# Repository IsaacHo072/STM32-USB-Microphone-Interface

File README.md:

# STM32-USB-Microphone-Interface
USB Audio Class Device with STM32G431CB and TLV320ADC6120

The PCB is working, but not fully verified since the I2C + I2S driver for TLV320ADC6120 haven't been written yet.

Some changes needed to be made to the STM32 board, for revision B:
 - Move all components to the top of the board, so it could be reflowed at once
 - Change the USB-C connector to a more popular and cheaper one
 - RST button have the wrong footprint, missing the positioning hole
 
Software development:
| Task                                                        | Status      | Finished?                                                                       |
|-------------------------------------------------------------|-------------|---------------------------------------------------------------------------------|
| Setup STM32G431 as a USB Audio Class Device in STM32CubeIDE | in progress | <ul><li>[x] USB could connect to PC </li><li>[ ] USB microphone mode </li></ul> |
| TLV320ADC6120 I2C Control                                   |             |                                                                                 |
| TLV320ADC6120 I2S transfer with DMA                         |             |                                                                                 |

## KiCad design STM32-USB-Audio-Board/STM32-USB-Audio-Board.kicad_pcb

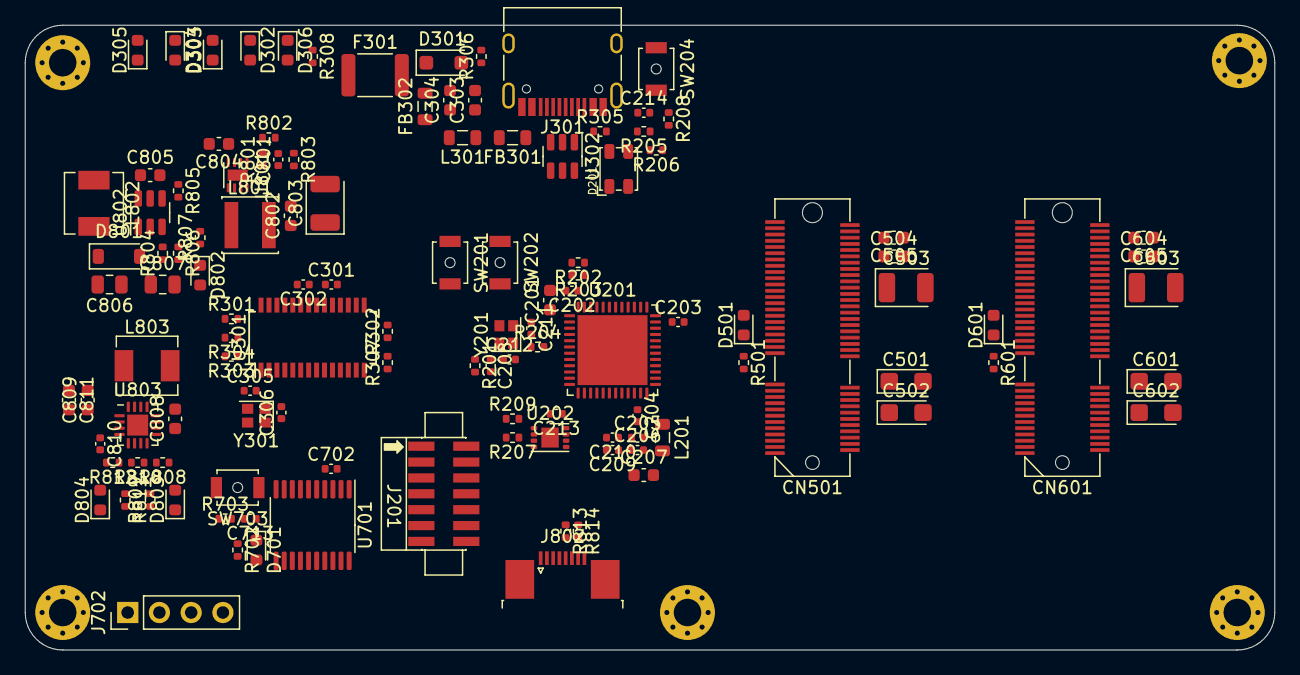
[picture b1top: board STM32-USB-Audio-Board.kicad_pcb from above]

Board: 4 copper layers, 100.0 x 50.0 mm, 125 parts (0 on the bottom side), 99 nets, no tracks yet.

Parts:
C201, C207, C303, C304, C802, C808, C811: 4.7uF; C_0603_1608Metric
C202, C203, C204, C206, C208, C210, C213, C214, C301, C302, C702, C810: 100nF; C_0402_1005Metric
C205: 1nF; C_0402_1005Metric
C209: 1uF; C_0402_1005Metric
C211, C212, C305, C306: 12pF; C_0402_1005Metric
C501, C502, C601, C602: 10uF; CP_EIA-3216-18_Kemet-A
C503, C603, C803: 10uF; CP_EIA-3528-21_Kemet-B
C504, C505, C604, C605, C804, C805, C809: 10uF; C_0603_1608Metric
C713: 10nF; C_0402_1005Metric
C801: 10pF; C_0402_1005Metric
C806, C807: 10uF; C_0805_2012Metric
CN501, CN601: Conn_02x38_Odd_Even; APCI0143-P001A
D201: LED_Dual_KAKA; LED_Dual_3528
D301: 20V; D_SOD-123F
D302, D303, D304, D305: GREEN; LED_0603_1608Metric
D306: RED; LED_0603_1608Metric
D501, D601, D701, D802, D803, D804: LED; LED_0603_1608Metric
D801: 3A/40V; D_SOD-123
F301: 2A; Fuse_1812_4532Metric
FB301, FB302: 100R; L_0805_2012Metric
H101, H102, H103, H104, H105: MountingHole_Pad; MountingHole_2.2mm_M2_Pad_Via
J201: Conn_ST_STDC14; STDC14_2x07_P1.27mm_Vertical_SMD
J301: USB_C_Receptacle_USB2.0; USB_C_Receptacle_HRO_TYPE-C-31-M-12
J702: Conn_01x04; PinHeader_1x04_P2.54mm_Vertical
J802: Conn_01x08; TE_0-1734839-8_1x08-1MP_P0.5mm_Horizontal
L201: 5R; L_0805_2012Metric
L301: 1.2uH; L_0805_2012Metric
L801: 1uH; L_Sunlord_SWPA4020S
L802: 10uH; L_Sunlord_MWSA0412S
L803: 2.2uH; L_Sunlord_MWSA0412S
R201: 0R; R_0402_1005Metric
R202, R203: 3.3k; R_0402_1005Metric
R204, R303, R304, R308, R702: 1k; R_0402_1005Metric
R205, R206: 2k; R_0402_1005Metric
R207, R209, R801, R802, R805: 100k; R_0402_1005Metric
R208, R301, R302, R703, R807: 10k; R_0402_1005Metric
R305, R306: 5.1k; R_0402_1005Metric
R307, R501, R601, R809, R811: 2.7k; R_0402_1005Metric
R803: 22.1k; R_0402_1005Metric
R804: 220k; R_0402_1005Metric
R806: 9.1k; R_0402_1005Metric
R808: 365k; R_0402_1005Metric
R810: 120k; R_0402_1005Metric
R812: 487k; R_0402_1005Metric
R813, R814: 100R; R_0402_1005Metric
SW201, SW202, SW204, SW703: SW_Push; SW_SPST_B3U-1000P-B
U201: STM32G431CBUx; QFN-48-1EP_7x7mm_P0.5mm_EP5.6x5.6mm
U202: W25Q16; SON-8-1EP_3x2mm_P0.5mm_EP1.4x1.6mm
U301: FE1.1s; SSOP-28_3.9x9.9mm_P0.635mm
U302: USBLC6-2SC6; SOT-23-6
U701: CH32V203F8P6; TSSOP-20_4.4x6.5mm_P0.65mm
U801: SY8883DFC; DFN-8-1EP_2x2mm_P0.5mm_EP0.9x1.6mm
U802: SY7208; SOT-23-6
U803: TPS65135; WQFN-16-1EP_3x3mm_P0.5mm_EP1.68x1.68mm
Y201: 8MHz; Crystal_SMD_2016-4Pin_2.0x1.6mm
Y301: 12MHz; Crystal_SMD_2016-4Pin_2.0x1.6mm

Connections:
+3.3V: C201.1, C202.1, C203.1, C204.1, C213.1, C501.1, C502.1, C601.1, C602.1, C702.1, C801.1, C802.1, C803.1, C809.1, CN501.18, CN501.20, CN501.22, CN601.18, CN601.20, CN601.22, D501.2 (A), D601.2 (A), J201.3 (VCC), J702.1, L201.1, L801.2, R202.2, R203.2, R205.1, R206.1, R208.2, R209.1, R703.1, R801.1, U201.1 (VBAT), U201.23 (VDD), U201.35 (VDD), U201.48 (VDD), U202.3 (IO2), U202.7 (IO3), U202.8 (VCC), U701.4 (VDD), U803.1 (VIN), U803.8 (EN)
+5V: C301.1, C804.1, C805.1, CN501.10, CN501.12, CN601.10, CN601.12, F301.1, J802.2, J802.3, L802.1, R802.1, R805.1, U301.18 (VBUSM), U301.20 (VDD5), U801.3 (IN), U802.5 (IN)
+5VA: C504.1, C604.1, C808.1, CN501.64, CN601.64, D803.2 (A), R808.1, U803.9 (OUTP), U803.10 (OUTP)
+15V: C503.1, C603.1, C806.1, C807.1, CN501.58, CN501.60, CN601.58, CN601.60, D801.1 (K), D802.2 (A), R804.1
-5VA: C505.2, C605.2, C811.2, CN501.70, CN601.70, D804.2 (A), R812.2, U803.2 (OUTN), U803.3 (OUTN)
/DAPLink CH32V203/LED_SWD: D701.2 (A), U701.12 (PA5)
/DAPLink CH32V203/RX1: J702.3, U701.20 (PA10)
/DAPLink CH32V203/SWD_RST: R201.1, U701.11 (PA4)
/DAPLink CH32V203/TX1: J702.2, U701.19 (PA9)
/DAPLink CH32V203/USB_DN: U301.10 (DM1), U701.1 (PB6)
/DAPLink CH32V203/USB_DP: U301.11 (DP1), U701.2 (PB7)
/HMI Sub-board Connector/Host_RX: R814.1, U201.24 (PB11)
/HMI Sub-board Connector/Host_TX: R813.1, U201.22 (PB10)
/Power Supply/3VEN: R802.2, U801.7 (EN)
/Power Supply/FB: C801.2, R801.2, R803.1, U801.1 (FB)
/Power Supply/LX: L801.1, U801.6 (LX)
/STM32G431CBU6/CARD_DETECT_0: CN501.23, U201.25 (PB12)
/STM32G431CBU6/CARD_DETECT_1: CN601.23, U201.26 (PB13)
/STM32G431CBU6/I2C1_SCL: CN501.54, CN601.54, R202.1, SW202.2, U201.46 (PB8)
/STM32G431CBU6/I2C1_SDA: CN501.52, CN601.52, R203.1, U201.47 (PB9)
/STM32G431CBU6/NRST: C208.2, J201.12 (~RST), R201.2, SW201.2, U201.7 (PG10)
/STM32G431CBU6/RCC_OSC_IN: C211.2, U201.5 (PF0), Y201.3
/STM32G431CBU6/RCC_OSC_OUT: R204.2, U201.6 (PF1)
/STM32G431CBU6/SAI-A-FS: CN501.36, U201.31 (PA9)
/STM32G431CBU6/SAI-A-GPIO0: CN501.46, U201.29 (PC6)
/STM32G431CBU6/SAI-A-GPIO1: CN501.48, U201.28 (PB15)
/STM32G431CBU6/SAI-A-MCLK: CN501.42, U201.11 (PA3)
/STM32G431CBU6/SAI-A-SCK: CN501.34, U201.30 (PA8)
/STM32G431CBU6/SAI-A-SD: CN501.38, U201.32 (PA10)
/STM32G431CBU6/SAI-B-FS: CN601.36, U201.44 (PB6)
/STM32G431CBU6/SAI-B-GPIO0: CN601.46, U201.39 (PC10)
/STM32G431CBU6/SAI-B-GPIO1: CN601.48, U201.40 (PC11)
/STM32G431CBU6/SAI-B-MCLK: CN601.42, U201.42 (PB4)
/STM32G431CBU6/SAI-B-SCK: CN601.34, U201.41 (PB3)
/STM32G431CBU6/SAI-B-SD: CN601.38, U201.43 (PB5)
/STM32G431CBU6/SPI_MISO: R207.1, U201.14 (PA6), U202.2 (DO(IO1))
/STM32G431CBU6/SPI_MOSI: U201.15 (PA7), U202.5 (DI(IO0))
/STM32G431CBU6/SPI_NSS: R209.2, U201.12 (PA4), U202.1 (~CS)
/STM32G431CBU6/SPI_SCK: U201.13 (PA5), U202.6 (CLK)
/STM32G431CBU6/SWCLK: J201.6 (JCLK/SWCLK), U201.37 (PA14), U701.7 (PA1)
/STM32G431CBU6/SWDIO: J201.4 (JTMS/SWDIO), U201.36 (PA13), U701.6 (PA0)
/STM32G431CBU6/USART1_RX: J201.13 (VCP_RX), U201.45 (PB7), U701.8 (PA2)
/STM32G431CBU6/USART1_TX: J201.14 (VCP_TX), U201.16 (PC4), U701.9 (PA3)
/STM32G431CBU6/USB_DN: U201.33 (PA11), U301.6 (DM3)
/STM32G431CBU6/USB_DP: U201.34 (PA12), U301.7 (DP3)
/STM32G431CBU6/USER_LED_G: D201.1 (A1), U201.18 (PB1)
/STM32G431CBU6/USER_LED_R: D201.3 (A2), U201.17 (PB0)
/STM32G431CBU6/VDDA: C205.1, C206.1, C207.1, L201.2, U201.21 (VDDA)
/STM32G431CBU6/VREF: C209.1, C210.1, U201.20 (VREF+)
/Sub-Board Connector 1/CARD_DETECT1: CN501.21, R501.2
/Sub-Board Connector 1/USB_DN: CN501.5, U301.8 (DM2)
/Sub-Board Connector 1/USB_DP: CN501.3, U301.9 (DP2)
/Sub-Board Connector 2/CARD_DETECT1: CN601.21, R601.2
/Sub-Board Connector 2/USB_DN: CN601.5, U301.4 (DM4)
/Sub-Board Connector 2/USB_DP: CN601.3, U301.5 (DP4)
/USB Connector/FE1.1_3.3V: C302.1, R301.1, R302.1, U301.21 (VD33_O)
/USB Connector/USB_DN: U301.15 (DMU), U302.6 (I/O1)
/USB Connector/USB_DP: U301.16 (DPU), U302.4 (I/O2)
/USB Connector/USBc_DN: J301.A7 (D-), J301.B7 (D-), U302.1 (I/O1)
/USB Connector/USBc_DP: J301.A6 (D+), J301.B6 (D+), U302.3 (I/O2)
/USB Connector/VBUS: D301.1 (A1), F301.2, FB302.2
/USB Connector/VBUS_{C}: FB301.1, J301.A4 (VBUS), J301.A9 (VBUS), J301.B4 (VBUS), J301.B9 (VBUS)
GND: C201.2, C202.2, C203.2, C204.2, C205.2, C206.2, C207.2, C208.1, C209.2, C210.2, C211.1, C212.1, C213.2, C214.1, C301.2, C302.2, C303.2, C304.2, C305.1, C306.1, C501.2, C502.2, C503.2, C504.2, C505.1, C601.2, C602.2, C603.2, C604.2, C605.1, C702.2, C713.1, C802.2, C803.2, C804.2, C805.2, C806.2, C807.2, C808.2, C809.2, C810.2, C811.1, CN501.1, CN501.2, CN501.4, CN501.6, CN501.7, CN501.8, CN501.9, CN501.11, CN501.13, CN501.14, CN501.15, CN501.16, CN501.17, CN501.19, CN501.32, CN501.33, CN501.35, CN501.37, CN501.39, CN501.41, CN501.43, CN501.44, CN501.45, CN501.47, CN501.49, CN501.50, CN501.51, CN501.53, CN501.55, CN501.56, CN501.57, CN501.59, CN501.61, CN501.62, CN501.63, CN501.65, CN501.66, CN501.67, CN501.68, CN501.69, CN501.71, CN501.72, CN501.73, CN501.74, CN501.75, CN601.1, CN601.2, CN601.4, CN601.6, CN601.7, CN601.8, CN601.9, CN601.11, CN601.13, CN601.14, CN601.15, CN601.16, CN601.17, CN601.19, CN601.32, CN601.33, CN601.35, CN601.37, CN601.39, CN601.41, CN601.43, CN601.44, CN601.45, CN601.47, CN601.49, CN601.50, CN601.51, CN601.53, CN601.55, CN601.56, CN601.57, CN601.59, CN601.61, CN601.62, CN601.63, CN601.65, CN601.66, CN601.67, CN601.68, CN601.69, CN601.71, CN601.72, CN601.73, CN601.74, CN601.75, D301.2 (A2), H101.1, H102.1, H103.1, H104.1, H105.1, J201.5 (GND), J201.7 (GND), J301.A1 (GND), J301.A12 (GND), J301.B1 (GND), J301.B12 (GND), J702.4, J802.1, J802.4, J802.6, J802.8, R207.2, R305.2, R306.2, R307.2, R308.2, R702.2, R803.2, R806.2, R807.2, R809.2, R811.2, SW201.1, SW202.1, SW204.1, SW703.2, U201.49 (VSS), U202.4 (GND), U301.1 (VSS), U301.19 (BUSJ), U302.2 (GND), U701.3 (VSS), U801.4 (PGND), U801.8 (AGND), U801.9 (PGND), U802.2 (GND), U803.5 (GND), U803.11 (PGND), U803.12 (PGND), U803.17 (EP), Y201.2, Y201.4, Y301.2, Y301.4
unnamed: C212.2, R204.1, Y201.1
unnamed: C303.1, FB301.2, L301.1
unnamed: C304.1, FB302.1, L301.2
unnamed: D201.2 (K1), R205.2
unnamed: D201.4 (K2), R206.2
unnamed: D302.2 (A), D303.1 (K), D304.2 (A), D305.1 (K), D306.2 (A), U301.22 (DRV)
unnamed: D302.1 (K), D303.2 (A), R303.2
unnamed: D304.1 (K), D305.2 (A), R304.2
unnamed: D306.1 (K), R308.1
unnamed: D501.1 (K), R501.1
unnamed: D601.1 (K), R601.1
unnamed: D701.1 (K), R702.1
unnamed: D801.2 (A), L802.2, U802.1 (LX)
unnamed: D802.1 (K), R807.1
unnamed: D803.1 (K), R809.1
unnamed: D804.1 (K), R811.1
unnamed: J301.A5 (CC1), R305.1
unnamed: J301.B5 (CC2), R306.1
unnamed: J802.5, R813.2
unnamed: J802.7, R814.2
unnamed: L803.1, U803.15 (L1), U803.16 (L1)
unnamed: L803.2, U803.13 (L2), U803.14 (L2)
unnamed: C214.2, R208.1, SW204.2, U201.27 (PB14)
unnamed: R303.1, U301.23 (LED1/EESCL)
unnamed: R304.1, U301.24 (LED2)
unnamed: R301.2, U301.26 (OVCJ)
unnamed: R307.1, U301.14 (REXT)
unnamed: C306.2, U301.3 (XIN), Y301.1
unnamed: C305.2, U301.2 (XOUT), Y301.3
unnamed: R302.2, U301.17 (~XRSTJ)
unnamed: C713.2, R703.2, SW703.1, U701.5 (NRST)
unnamed: R805.2, U802.4 (EN)
unnamed: R804.2, R806.1, U802.3 (FB)
unnamed: R808.2, R810.1, U803.7 (FB)
unnamed: R810.2, R812.1, U803.6 (FBG)
unnamed: C810.1, U803.4 (VAUX)

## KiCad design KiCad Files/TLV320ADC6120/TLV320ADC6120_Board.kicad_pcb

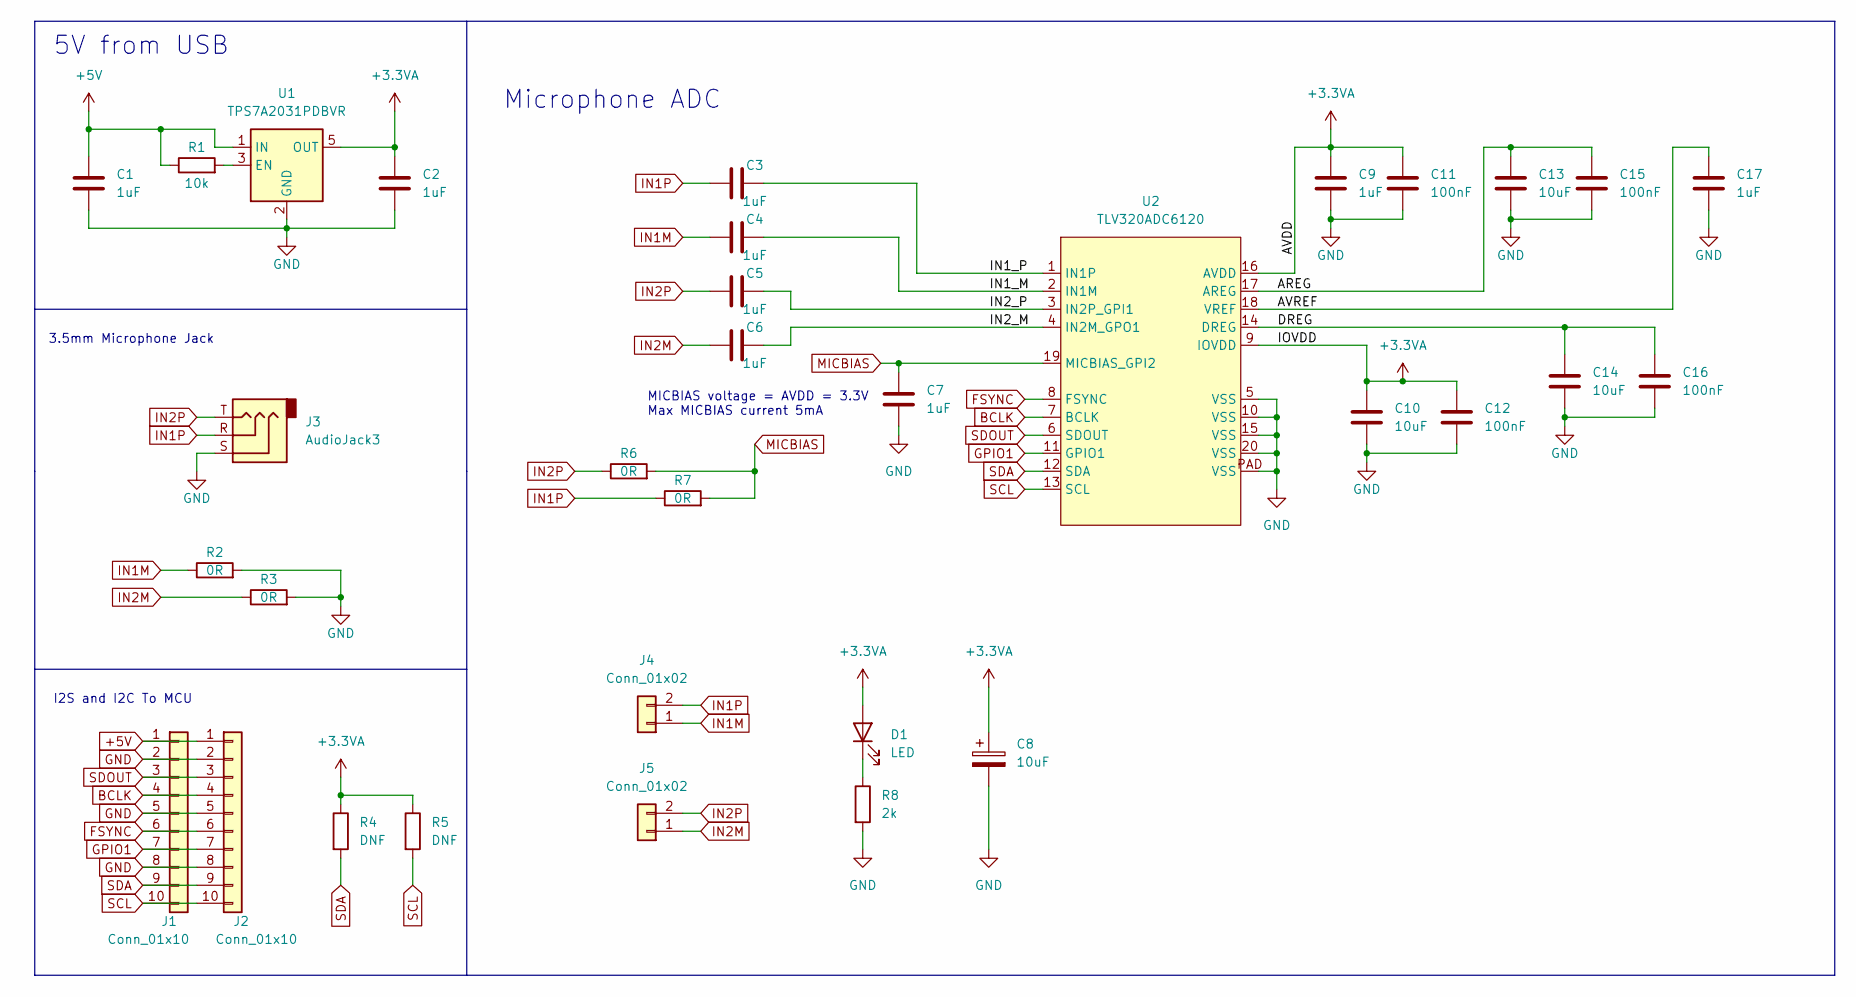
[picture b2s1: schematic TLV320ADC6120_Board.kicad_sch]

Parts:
C1, C2, C7, C9, C17: 1uF; C_0603_1608Metric
C3, C4, C5, C6: 1uF; C_1206_3216Metric
C8: 10uF; CP_EIA-3216-18_Kemet-A
C10, C13, C14: 10uF; C_0603_1608Metric
C11, C12, C15, C16: 100nF; C_0402_1005Metric
D1: LED; LED_0603_1608Metric
J1: Conn_01x10; JST_PH_S10B-PH-SM4-TB_1x10-1MP_P2.00mm_Horizontal
J2: Conn_01x10; PinHeader_1x10_P2.00mm_Vertical
J3: AudioJack3; Jack_3.5mm_CUI_SJ-3523-SMT_Horizontal
J4, J5: Conn_01x02; JST_PH_B2B-PH-SM4-TB_1x02-1MP_P2.00mm_Vertical
R1: 10k; R_0603_1608Metric
R2, R3, R6, R7: 0R; R_0603_1608Metric
R4, R5: DNF; R_0603_1608Metric
R8: 2k; R_0603_1608Metric
U1: TPS7A2031PDBVR; SOT-23-5
U2: TLV320ADC6120; QFN-16_EP_3x3_Pitch0.5mm

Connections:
+3.3VA: C2.1, C8.1, C9.1, C10.1, C11.1, C12.1, D1.2 (A), R4.1, R5.1, U1.5 (OUT), U2.9 (IOVDD), U2.16 (AVDD)
+5V: C1.1, J1.1, J2.1, R1.1, U1.1 (IN)
/AREG: C13.1, C15.1, U2.17 (AREG)
/AVREF: C17.1, U2.18 (VREF)
/DREG: C14.1, C16.1, U2.14 (DREG)
/IN1_M: C4.2, U2.2 (IN1M)
/IN1_P: C3.2, U2.1 (IN1P)
/IN2_M: C6.2, U2.4 (IN2M_GPO1)
/IN2_P: C5.2, U2.3 (IN2P_GPI1)
BCLK: J1.4, J2.4, U2.7 (BCLK)
FSYNC: J1.6, J2.6, U2.8 (FSYNC)
GND: C1.2, C2.2, C7.2, C8.2, C9.2, C10.2, C11.2, C12.2, C13.2, C14.2, C15.2, C16.2, C17.2, J1.2, J1.5, J1.8, J2.2, J2.5, J2.8, J3.S, R2.2, R3.2, R8.2, U1.2 (GND), U2.5 (VSS), U2.10 (VSS), U2.15 (VSS), U2.20 (VSS), U2.PAD (VSS)
GPIO1: J1.7, J2.7, U2.11 (GPIO1)
IN1M: C4.1, J4.1, R2.1
IN1P: C3.1, J3.R, J4.2, R7.1
IN2M: C6.1, J5.1, R3.1
IN2P: C5.1, J3.T, J5.2, R6.1
MICBIAS: C7.1, R6.2, R7.2, U2.19 (MICBIAS_GPI2)
unnamed: D1.1 (K), R8.1
unnamed: R1.2, U1.3 (EN)
SCL: J1.10, J2.10, R5.2, U2.13 (SCL)
SDA: J1.9, J2.9, R4.2, U2.12 (SDA)
SDOUT: J1.3, J2.3, U2.6 (SDOUT)

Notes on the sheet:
3.5mm Microphone Jack
MICBIAS voltage = AVDD = 3.3V Max MICBIAS current 5mA
I2S and I2C To MCU
5V from USB
Microphone ADC

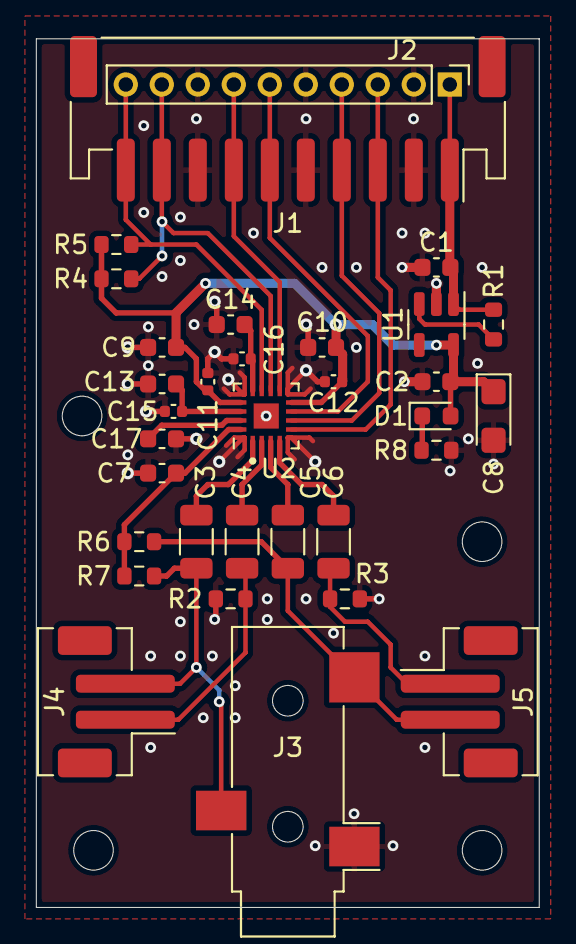
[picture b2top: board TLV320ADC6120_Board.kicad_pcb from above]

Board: 2 copper layers, 27.9 x 48.3 mm, 33 parts (0 on the bottom side), 23 nets.

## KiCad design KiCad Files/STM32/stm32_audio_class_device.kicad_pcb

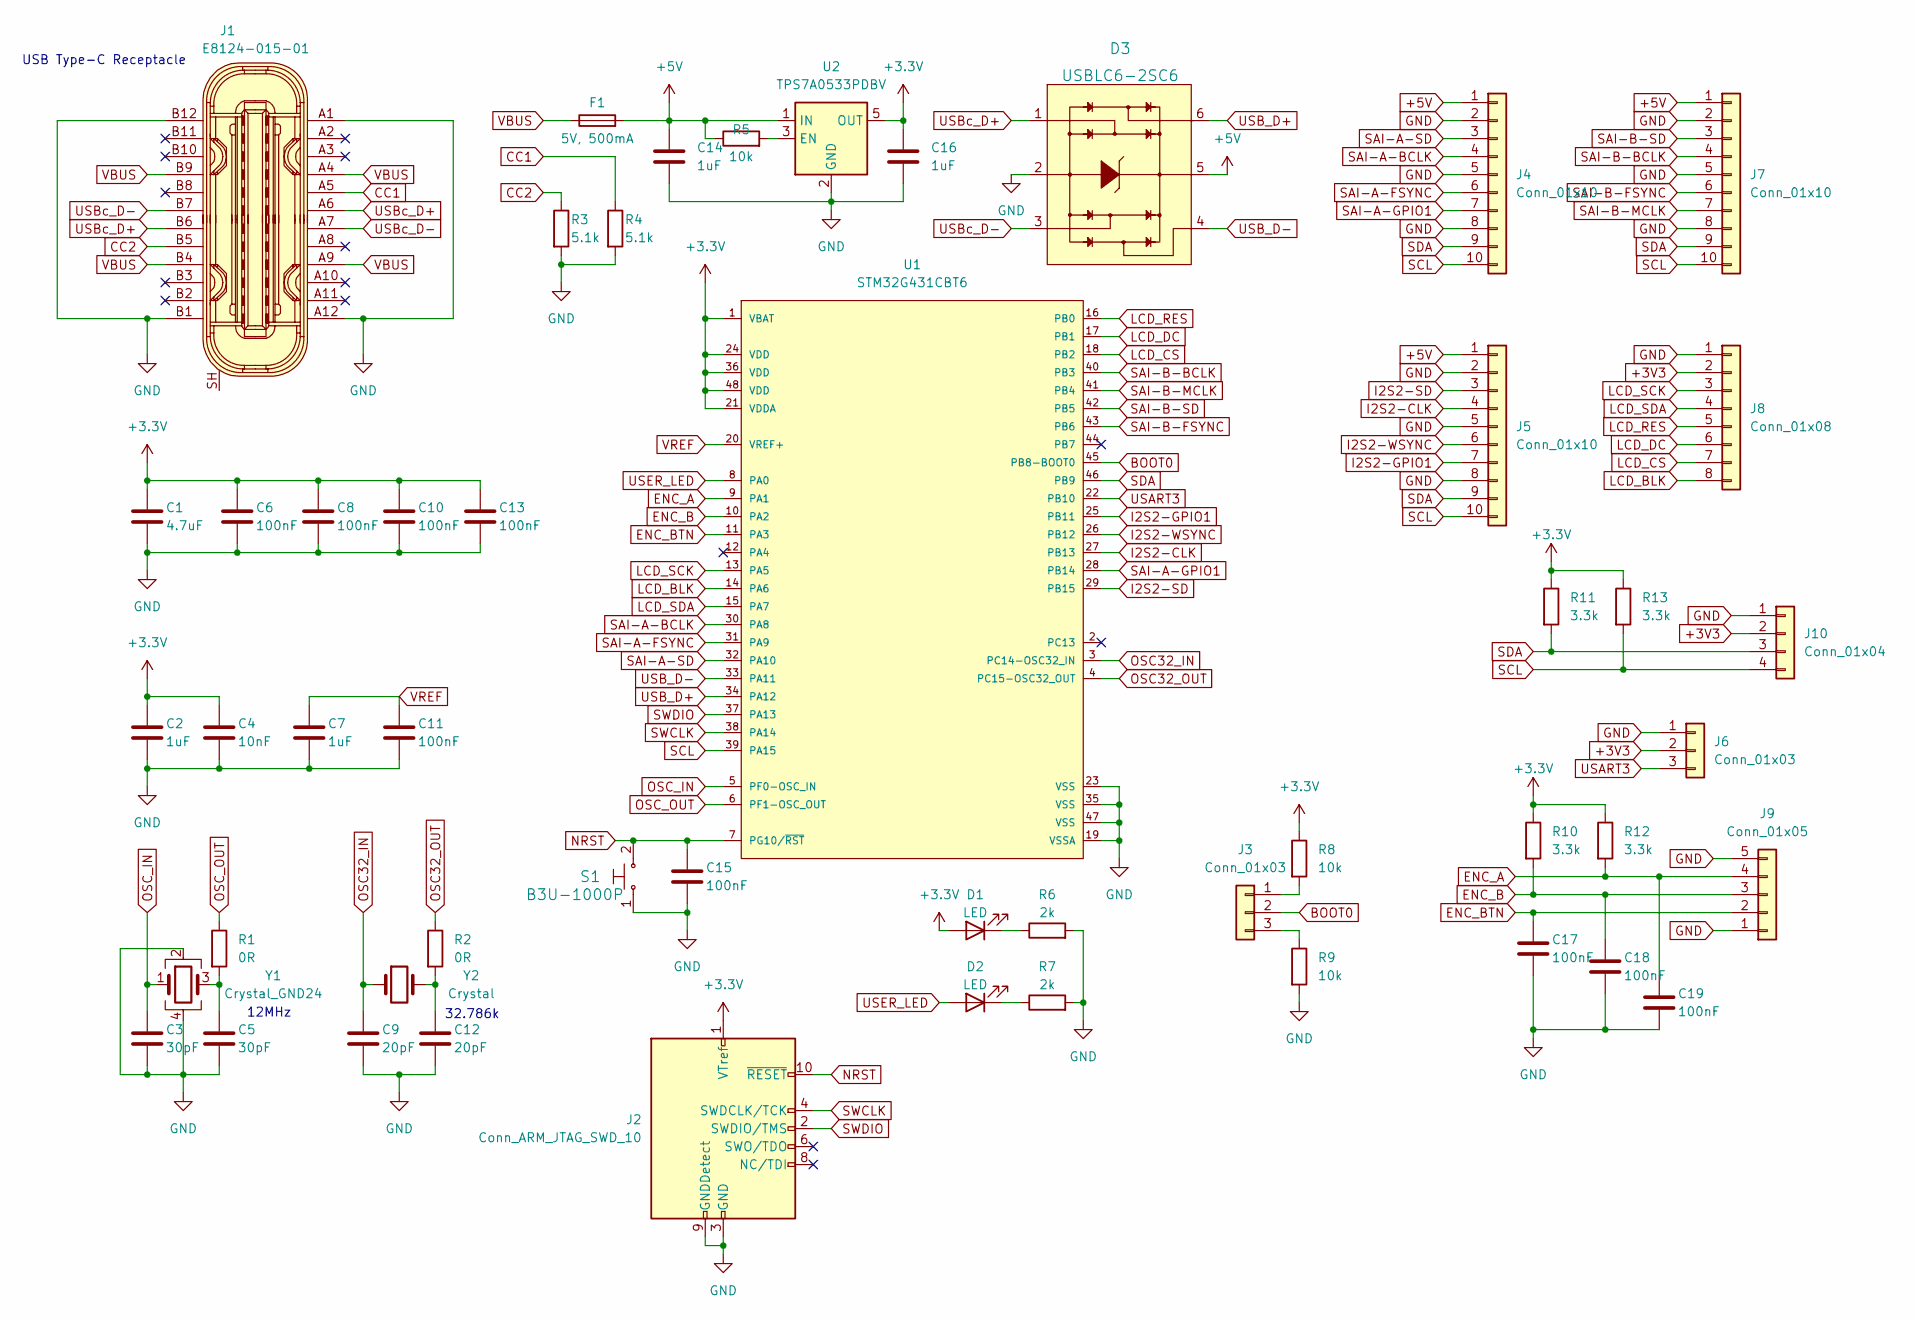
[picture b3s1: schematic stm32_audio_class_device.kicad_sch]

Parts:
C1: 4.7uF; C_0805_2012Metric
C2, C7, C14, C16: 1uF; C_0603_1608Metric
C3, C5: 30pF; C_0603_1608Metric
C4: 10nF; C_0603_1608Metric
C6, C8, C10, C11, C13, C15, C17, C18, C19: 100nF; C_0603_1608Metric
C9, C12: 20pF; C_0603_1608Metric
D1, D2: LED; LED_0603_1608Metric
D3: USBLC6-2SC6; SOT23-6L; MPN USBLC6-2SC6; Digi-Key_PN 497-5235-1-ND
F1: 5V, 500mA; Fuse_0805_2012Metric
J1: E8124-015-01; USB-C_Female_E8124-015-01; MPN E8124-015-01; Digi-Key_PN 553-3195-1-ND
J2: Conn_ARM_JTAG_SWD_10; PinHeader_2x05_P1.27mm_Vertical
J3, J6: Conn_01x03; PinHeader_1x03_P2.54mm_Vertical
J4, J5, J7: Conn_01x10; JST_PH_B10B-PH-K_1x10_P2.00mm_Vertical
J8: Conn_01x08; JST_PH_B8B-PH-K_1x08_P2.00mm_Vertical
J9: Conn_01x05; JST_PH_B5B-PH-K_1x05_P2.00mm_Vertical
J10: Conn_01x04; JST_PH_B4B-PH-K_1x04_P2.00mm_Vertical
R1, R2: 0R; R_0603_1608Metric
R3, R4: 5.1k; R_0603_1608Metric
R5, R8, R9: 10k; R_0603_1608Metric
R6, R7: 2k; R_0603_1608Metric
R10, R11, R12, R13: 3.3k; R_0603_1608Metric
S1: B3U-1000P; Switch_Tactile_SMD_B3U-1000P; MPN B3U-1000P; Digi-Key_PN SW1020CT-ND
U1: STM32G431CBT6; STMicroelectronics-LQFP48-5B-0-2-MFG; mouser part number 511-STM32G431CBT6; digikey description MAINSTREAM ARM CORTEX-M4+ MCU 17
U2: TPS7A0533PDBV; SOT-23-5
Y1: Crystal_GND24; Crystal_SMD_3225-4Pin_3.2x2.5mm
Y2: Crystal; Crystal_SMD_3215-2Pin_3.2x1.5mm

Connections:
+5V: C14.1, D3.5, F1.2, J4.1, J5.1, J7.1, R5.1, U2.1 (IN)
BOOT0: J3.2, U1.45 (PB8-BOOT0)
CC1: J1.A5, R4.1
CC2: J1.B5, R3.1
ENC_A: C19.1, J9.4, R12.2, U1.9 (PA1)
ENC_B: C18.1, J9.3, R10.2, U1.10 (PA2)
ENC_BTN: C17.1, J9.2, U1.11 (PA3)
GND: C1.2, C2.2, C3.2, C4.2, C5.2, C6.2, C7.2, C8.2, C9.2, C10.2, C11.2, C12.2, C13.2, C14.2, C15.2, C16.2, C17.2, C18.2, C19.2, D3.2, J1.A1, J1.A12, J1.B1, J1.B12, J2.3 (GND), J2.5 (GND), J2.9 (GNDDetect), J4.2, J4.5, J4.8, J5.2, J5.5, J5.8, J6.1, J7.2, J7.5, J7.8, J8.1, J9.1, J9.5, J10.1, R3.2, R4.2, R6.2, R7.2, R9.2, S1.1, U1.19 (VSSA), U1.23 (VSS), U1.35 (VSS), U1.47 (VSS), U2.2 (GND), Y1.2, Y1.4
I2S2-CLK: J5.4, U1.27 (PB13)
I2S2-GPIO1: J5.7, U1.25 (PB11)
I2S2-SD: J5.3, U1.29 (PB15)
I2S2-WSYNC: J5.6, U1.26 (PB12)
LCD_BLK: J8.8, U1.14 (PA6)
LCD_CS: J8.7, U1.18 (PB2)
LCD_DC: J8.6, U1.17 (PB1)
LCD_RES: J8.5, U1.16 (PB0)
LCD_SCK: J8.3, U1.13 (PA5)
LCD_SDA: J8.4, U1.15 (PA7)
NRST: C15.1, J2.10 (~RESET), S1.2, U1.7 (PG10/~RST)
unnamed: C5.1, R1.2, Y1.3
unnamed: C12.1, R2.2, Y2.2
unnamed: D1.1 (K), R6.1
unnamed: D2.1 (K), R7.1
unnamed: J3.1, R8.2
unnamed: J3.3, R9.1
unnamed: R5.2, U2.3 (EN)
OSC32_IN: C9.1, U1.3 (PC14-OSC32_IN), Y2.1
OSC32_OUT: R2.1, U1.4 (PC15-OSC32_OUT)
OSC_IN: C3.1, U1.5 (PF0-OSC_IN), Y1.1
OSC_OUT: R1.1, U1.6 (PF1-OSC_OUT)
SAI-A-BCLK: J4.4, U1.30 (PA8)
SAI-A-FSYNC: J4.6, U1.31 (PA9)
SAI-A-GPIO1: J4.7, U1.28 (PB14)
SAI-A-SD: J4.3, U1.32 (PA10)
SAI-B-BCLK: J7.4, U1.40 (PB3)
SAI-B-FSYNC: J7.6, U1.43 (PB6)
SAI-B-MCLK: J7.7, U1.41 (PB4)
SAI-B-SD: J7.3, U1.42 (PB5)
SCL: J4.10, J5.10, J7.10, J10.4, R13.2, U1.39 (PA15)
SDA: J4.9, J5.9, J7.9, J10.3, R11.2, U1.46 (PB9)
SWCLK: J2.4 (SWDCLK/TCK), U1.38 (PA14)
SWDIO: J2.2 (SWDIO/TMS), U1.37 (PA13)
USART3: J6.3, U1.22 (PB10)
USB_D+: D3.6, U1.34 (PA12)
USB_D-: D3.4, U1.33 (PA11)
USBc_D+: D3.1, J1.A6, J1.B6
USBc_D-: D3.3, J1.A7, J1.B7
USER_LED: D2.2 (A), U1.8 (PA0)
VBUS: F1.1, J1.A4, J1.A9, J1.B4, J1.B9
VREF: C7.1, C11.1, U1.20 (VREF+)

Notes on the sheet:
32.786k
USB Type-C Receptacle
12MHz

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
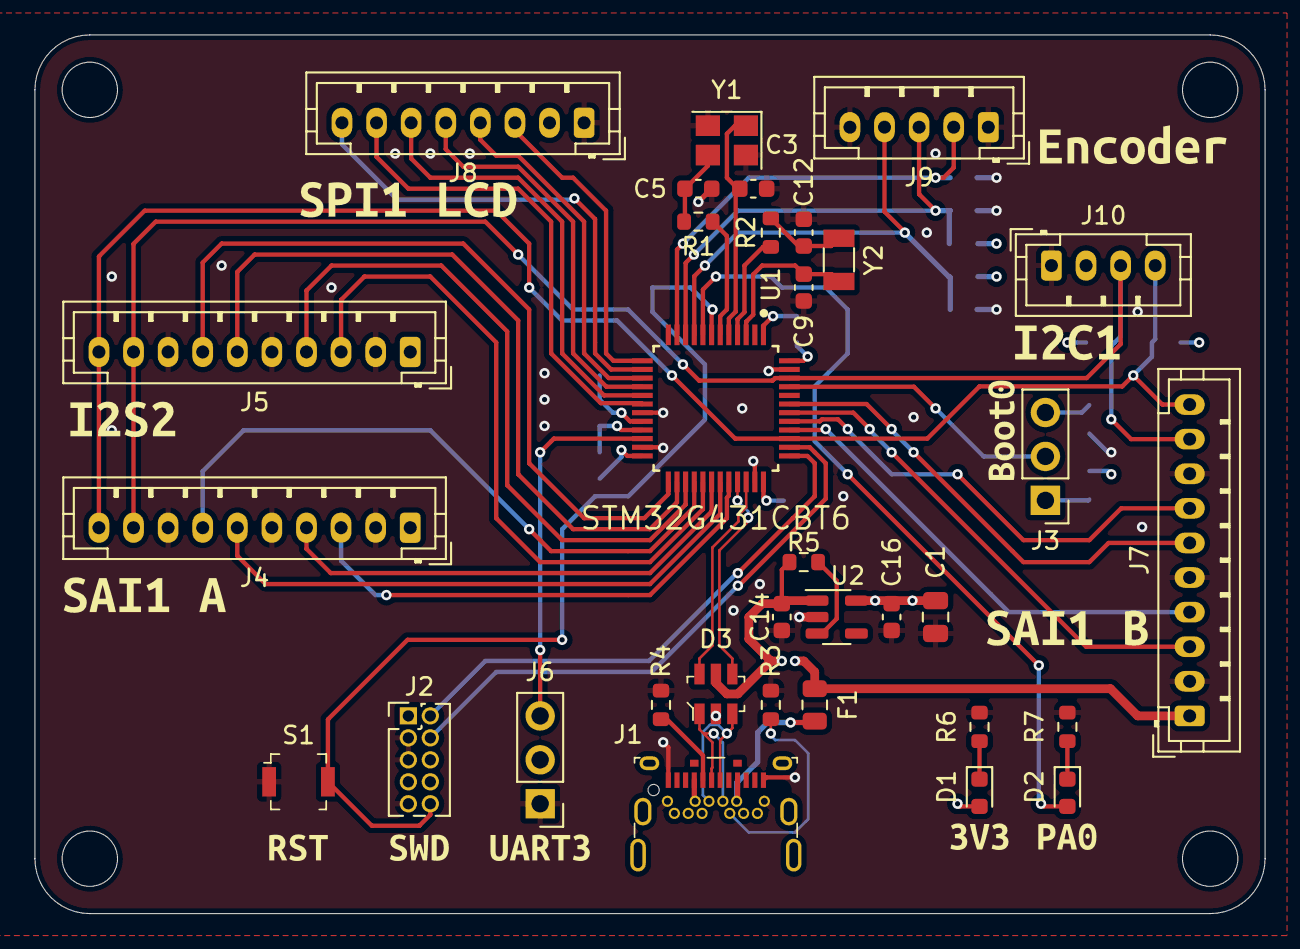
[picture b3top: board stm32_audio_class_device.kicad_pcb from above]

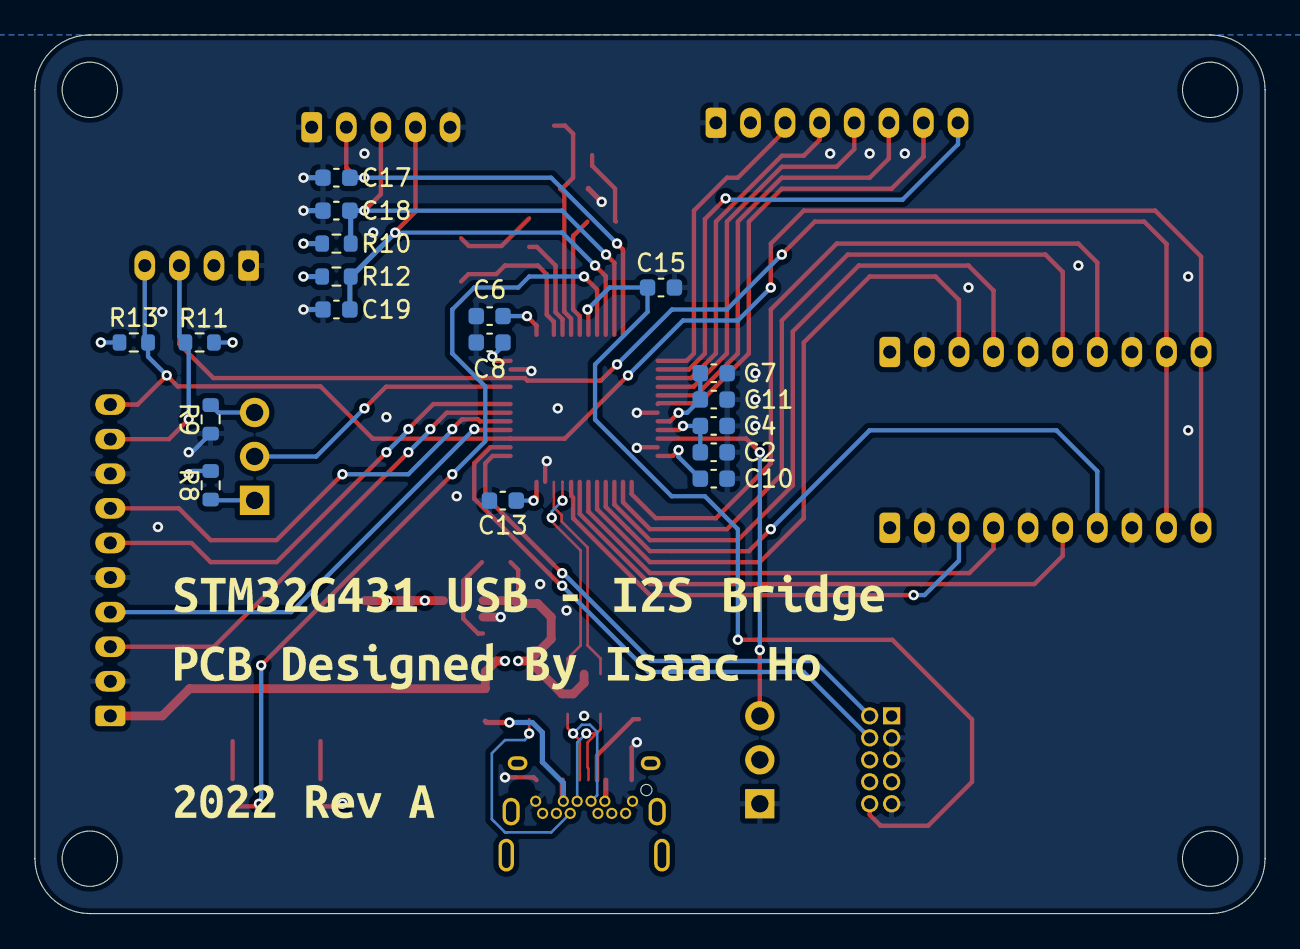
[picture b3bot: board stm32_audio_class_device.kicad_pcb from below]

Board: 4 copper layers, 71.1 x 50.8 mm, 64 parts (19 on the bottom side), 51 nets.

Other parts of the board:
kibuzzard-620D2A22: G***; kibuzzard-620D2A22
kibuzzard-620D28C3: G***; kibuzzard-620D28C3
kibuzzard-620D28D6: G***; kibuzzard-620D28D6
kibuzzard-620D28EA: G***; kibuzzard-620D28EA
kibuzzard-620D29A8: G***; kibuzzard-620D29A8
kibuzzard-620D29B6: G***; kibuzzard-620D29B6
kibuzzard-620D288B: G***; kibuzzard-620D288B
kibuzzard-620D295B: G***; kibuzzard-620D295B
kibuzzard-620D2901: G***; kibuzzard-620D2901
kibuzzard-620D2924: G***; kibuzzard-620D2924
kibuzzard-620D2934: G***; kibuzzard-620D2934
kibuzzard-620D2952: G***; kibuzzard-620D2952
kibuzzard-620D2969: G***; kibuzzard-620D2969

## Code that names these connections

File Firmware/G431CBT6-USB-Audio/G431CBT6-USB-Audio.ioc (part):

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Mcu.Name=STM32G431C(6-8-B)Tx
Mcu.Package=LQFP48
Mcu.UserName=STM32G431CBTx
PA0.GPIOParameters=GPIO_Label
PA0.GPIO_Label=LED
PA0.Signal=GPIO_Output
PA1.GPIOParameters=GPIO_Label
PA1.GPIO_Label=ENC_A
PA1.Signal=GPIO_Input
PA11.Mode=Device
PA11.Signal=USB_DM
PA12.Mode=Device
PA12.Signal=USB_DP
PA13.Mode=Serial_Wire
PA13.Signal=SYS_JTMS-SWDIO
PA14.Mode=Serial_Wire
PA14.Signal=SYS_JTCK-SWCLK
PA15.Mode=I2C
PA15.Signal=I2C1_SCL
PA2.GPIOParameters=GPIO_Label
PA2.GPIO_Label=ENC_B
PA2.Signal=GPIO_Input
PA3.GPIOParameters=GPIO_PuPd,GPIO_Label,GPIO_ModeDefaultEXTI
PA3.GPIO_Label=ENC_BTN
PA3.GPIO_ModeDefaultEXTI=GPIO_MODE_IT_FALLING
PA3.GPIO_PuPd=GPIO_PULLUP
PA3.Signal=GPXTI3
PA5.GPIOParameters=GPIO_Label
PA5.GPIO_Label=LCD_SCK
PA5.Mode=TX_Only_Simplex_Unidirect_Master
PA5.Signal=SPI1_SCK
PA6.GPIOParameters=GPIO_Label
PA6.GPIO_Label=LCD_BLK
PA6.Signal=GPIO_Output
PA7.GPIOParameters=GPIO_Label
PA7.GPIO_Label=LCD_SDA
PA7.Mode=TX_Only_Simplex_Unidirect_Master
PA7.Signal=SPI1_MOSI
PB0.GPIOParameters=GPIO_Label
PB0.GPIO_Label=LCD_RST
PB0.Signal=GPIO_Output
PB1.GPIOParameters=GPIO_Label
PB1.GPIO_Label=LCD_DC
PB1.Signal=GPIO_Output
PB2.GPIOParameters=GPIO_Label
PB2.GPIO_Label=LCD_CS
PB2.Signal=GPIO_Output
PB3.Mode=SAI_B_MasterWithClock
PB3.Signal=SAI1_SCK_B
PB4.Mode=SAI_B_MasterWithClock
PB4.Signal=SAI1_MCLK_B
PB5.Mode=SAI_B_MasterWithClock
PB5.Signal=SAI1_SD_B
PB6.Mode=SAI_B_MasterWithClock
PB6.Signal=SAI1_FS_B
PB9.Mode=I2C
PB9.Signal=I2C1_SDA
PC14-OSC32_IN.Mode=LSE-External-Oscillator
PC14-OSC32_IN.Signal=RCC_OSC32_IN
PC15-OSC32_OUT.Mode=LSE-External-Oscillator
PC15-OSC32_OUT.Signal=RCC_OSC32_OUT
PF0-OSC_IN.Mode=HSE-External-Oscillator
PF0-OSC_IN.Signal=RCC_OSC_IN
PF1-OSC_OUT.Mode=HSE-External-Oscillator
PF1-OSC_OUT.Signal=RCC_OSC_OUT
RCC.HSE_VALUE=12000000
RCC.SYSCLKFreq_VALUE=96000000
RCC.SYSCLKSource=RCC_SYSCLKSOURCE_PLLCLK
board=custom

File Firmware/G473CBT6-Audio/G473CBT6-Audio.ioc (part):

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Mcu.Name=STM32G473C(B-C-E)Tx
Mcu.Package=LQFP48
Mcu.UserName=STM32G473CBTx
PA0.GPIOParameters=GPIO_Label
PA0.GPIO_Label=USER_LED
PA0.Signal=GPIO_Output
PA1.GPIOParameters=GPIO_Label
PA1.GPIO_Label=ENC_A
PA1.Signal=GPIO_Input
PA11.Mode=Device
PA11.Signal=USB_DM
PA12.Mode=Device
PA12.Signal=USB_DP
PA13.Mode=Serial_Wire
PA13.Signal=SYS_JTMS-SWDIO
PA14.Mode=Serial_Wire
PA14.Signal=SYS_JTCK-SWCLK
PA15.Mode=I2C
PA15.Signal=I2C1_SCL
PA2.GPIOParameters=GPIO_Label
PA2.GPIO_Label=ENC_B
PA2.Signal=GPIO_Input
PA3.GPIOParameters=GPIO_Label
PA3.GPIO_Label=ENC_BTN
PA3.Signal=GPIO_Input
PA5.Mode=TX_Only_Simplex_Unidirect_Master
PA5.Signal=SPI1_SCK
PA6.GPIOParameters=GPIO_Label
PA6.GPIO_Label=LCD_BLK
PA6.Signal=GPIO_Output
PA7.Mode=TX_Only_Simplex_Unidirect_Master
PA7.Signal=SPI1_MOSI
PB0.GPIOParameters=GPIO_Label
PB0.GPIO_Label=LCD_RES
PB0.Signal=GPIO_Output
PB1.GPIOParameters=GPIO_Label
PB1.GPIO_Label=LCD_DC
PB1.Signal=GPIO_Output
PB10.Mode=Half_duplex(single_wire_mode)
PB10.Signal=USART3_TX
PB2.GPIOParameters=GPIO_Label
PB2.GPIO_Label=LCD_CS
PB2.Signal=GPIO_Output
PB3.Mode=SAI_B_MasterWithClock
PB3.Signal=SAI1_SCK_B
PB4.Mode=SAI_B_MasterWithClock
PB4.Signal=SAI1_MCLK_B
PB5.Mode=SAI_B_MasterWithClock
PB5.Signal=SAI1_SD_B
PB6.Mode=SAI_B_MasterWithClock
PB6.Signal=SAI1_FS_B
PB9.Mode=I2C
PB9.Signal=I2C1_SDA
PF0-OSC_IN.Mode=HSE-External-Oscillator
PF0-OSC_IN.Signal=RCC_OSC_IN
PF1-OSC_OUT.Mode=HSE-External-Oscillator
PF1-OSC_OUT.Signal=RCC_OSC_OUT
RCC.HSE_VALUE=8000000
RCC.SYSCLKFreq_VALUE=128000000
RCC.SYSCLKSource=RCC_SYSCLKSOURCE_PLLCLK
board=custom

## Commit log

2022-02-17 Added KiCad design files
2022-04-07 Fix part number
    TLV320ADC6120 mistakenly labelled as a second TPS7A0533PDBV
2022-04-07 Fix part number
    Changed mislabeled
    TPS7A0533PDBV to TPS7A2031PDBVR on the TLV320ADC6120 board
2022-04-07 Updated Readme
    Updated project info in readme, added pcb picture
2023-04-15 New V2 branch
2023-04-15 Moved sub-board folder to root directory
2023-08-11 Cleanup
2023-08-11 Add firmware source folder
2023-08-11 Add firmware source folder for G431
